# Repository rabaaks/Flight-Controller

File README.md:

# Custom Flight Controller

This is a custom flight controller and camera system that I designed to be used with Ardupilot for a drone or airplane. I made this to learn more about PCB design and also because I wanted a flight controller that I could use for my RC plane, so that I could setup autonomous flight and have better telemetry. I also wanted specific peripherals like the led strip and an OSD.

## Features

* STM32H743 Microcontroller
* BMP388 Pressure Sensor
* QMC5883 Magnetometeter
* ICM-42688 IMU
* OSD using MAX7456
* LED Strip
* 12 Motor Ouputs
* MicroSD Card
* 6 UARTs and 1 I2C

## Schematic

## PCB

## Render

I also designed a basic camera system to be used with it, using RX5808 and TX5823S modules. It uses a camera and display from a car backup camera system which was a low cost option that uses analog video. The camera and display require 12v, while the radio modules require 5v, so some voltage conversion is necessary. This circuit will be assembled on 0.1" pitch perfboard.

## Bill of Materials

|Name                                                               |Quantity|Unit Price|Total Price|Link                                                |FIELD6|Total Price|
|-------------------------------------------------------------------|--------|----------|-----------|----------------------------------------------------|------|-----------|
|CL10B105KA8NNNC                                                    |50      |0.0062    |0.31       |https://www.lcsc.com/product-detail/C29936.html     |      |71.26      |
|CL10B104KB8NNNC                                                    |100     |0.0027    |0.27       |https://www.lcsc.com/product-detail/C1591.html      |      |           |
|CL21B475KOFNNNE                                                    |10      |0.0191    |0.19       |https://www.lcsc.com/product-detail/C107365.html    |      |           |
|CL21B106KOQNNNE                                                    |10      |0.0247    |0.25       |https://www.lcsc.com/product-detail/C95841.html     |      |           |
|CL10C120JB8NNNC                                                    |100     |0.0047    |0.47       |https://www.lcsc.com/product-detail/C38523.html     |      |           |
|CL10B225KP8NNNC                                                    |50      |0.0123    |0.62       |https://www.lcsc.com/product-detail/C100082.html    |      |           |
|CL10C180JB8NNNC                                                    |100     |0.005     |0.5        |https://www.lcsc.com/product-detail/C1647.html      |      |           |
|CL10C470JB8NNNC                                                    |100     |0.0031    |0.31       |https://www.lcsc.com/product-detail/C1671.html      |      |           |
|CL31A226KOHNNNE                                                    |5       |0.0381    |0.19       |https://www.lcsc.com/product-detail/C90146.html     |      |           |
|CL21B104KBCNNNC                                                    |50      |0.0065    |0.33       |https://www.lcsc.com/product-detail/C1711.html      |      |           |
|SS54                                                               |10      |0.0433    |0.43       |https://www.lcsc.com/product-detail/C22452.html     |      |           |
|WS2812B-B/T                                                        |5       |0.0879    |0.44       |https://www.lcsc.com/product-detail/C2761795.html   |      |           |
|NCD0805R1                                                          |50      |0.0125    |0.63       |https://www.lcsc.com/product-detail/C84256.html     |      |           |
|ZX-XH2.54-3PZZ                                                     |20      |0.01      |0.2        |https://www.lcsc.com/product-detail/C7429633.html   |      |           |
|XT30PW-M30.G.Y                                                     |1       |0.2926    |0.29       |https://www.lcsc.com/product-detail/C431092.html    |      |           |
|TYPE-C 16PIN 2MD(073)                                              |20      |0.06      |1.2        |https://www.lcsc.com/product-detail/C2765186.html   |      |           |
|ZX-XH2.54-6PZZ                                                     |20      |0.0198    |0.4        |https://www.lcsc.com/product-detail/C7429636.html   |      |           |
|ZX-XH2.54-4PZZ                                                     |20      |0.0111    |0.22       |https://www.lcsc.com/product-detail/C7429634.html   |      |           |
|ZX-XH2.54-10PZZ                                                    |10      |0.0434    |0.43       |https://www.lcsc.com/product-detail/C7429640.html   |      |           |
|TF PUSH                                                            |10      |0.0568    |0.57       |https://www.lcsc.com/product-detail/C393941.html    |      |           |
|APH0630T6R8M                                                       |10      |0.0633    |0.63       |https://www.lcsc.com/product-detail/C5349706.html   |      |           |
|0603WAF5601T5E                                                     |100     |0.0012    |0.12       |https://www.lcsc.com/product-detail/C23189.html     |      |           |
|0603WAF1001T5E                                                     |100     |0.0012    |0.12       |https://www.lcsc.com/product-detail/C21190.html     |      |           |
|0603WAF5101T5E                                                     |100     |0.0012    |0.12       |https://www.lcsc.com/product-detail/C23186.html     |      |           |
|0603WAF1003T5E                                                     |100     |0.0011    |0.11       |https://www.lcsc.com/product-detail/C25803.html     |      |           |
|0603WAF750JT5E                                                     |100     |0.0013    |0.13       |https://www.lcsc.com/product-detail/C4275.html      |      |           |
|0603WAF1002T5E                                                     |100     |0.0011    |0.11       |https://www.lcsc.com/product-detail/C25804.html     |      |           |
|0603WAF3301T5E                                                     |100     |0.0012    |0.12       |https://www.lcsc.com/product-detail/C22978.html     |      |           |
|0603WAF2202T5E                                                     |100     |0.0012    |0.12       |https://www.lcsc.com/product-detail/C31850.html     |      |           |
|TPS54302DDCR                                                       |5       |0.1517    |0.76       |https://www.lcsc.com/product-detail/C311983.html    |      |           |
|BMP388                                                             |1       |2.7418    |2.74       |https://www.lcsc.com/product-detail/C779278.html    |      |           |
|QMC5883P                                                           |1       |1.48      |1.48       |https://www.lcsc.com/product-detail/C2847467.html   |      |           |
|STM32H743VIT6                                                      |1       |7.1333    |7.13       |https://www.lcsc.com/product-detail/C114409.html    |      |           |
|AT7456ELAH                                                         |1       |3.9151    |3.92       |https://www.lcsc.com/product-detail/C42388749.html  |      |           |
|ICM-42688-PC                                                       |1       |2.0211    |2.02       |https://www.lcsc.com/product-detail/C48586483.html  |      |           |
|X322527MSB4SI                                                      |10      |0.0718    |0.72       |https://www.lcsc.com/product-detail/C9008.html      |      |           |
|X322516MLB4SI                                                      |10      |0.0678    |0.68       |https://www.lcsc.com/product-detail/C13738.html     |      |           |
|X321532768KGD2SI                                                   |5       |0.2164    |1.08       |https://www.lcsc.com/product-detail/C620155.html    |      |           |
|KM477M025F12RR0VH2FP0                                              |10      |0.0393    |0.39       |https://www.lcsc.com/product-detail/C43839.html     |      |           |
|LED Strip 5m                                                       |1       |8.46      |8.46       |https://www.aliexpress.us/item/3256807796309465.html|      |           |
|MT3608 5pcs                                                        |1       |2.49      |2.49       |https://www.aliexpress.us/item/3256806175499915.html|      |           |
|MP1584 5pcs                                                        |1       |5.5       |5.5        |https://www.aliexpress.us/item/3256805119457659.html|      |           |
|RX5808                                                             |1       |12.76     |12.76      |https://www.aliexpress.us/item/3256808812641407.html|      |           |
|TX5823S                                                            |1       |9.07      |9.07       |https://www.aliexpress.us/item/3256808812641407.html|      |           |
|VS-S4301                                                           |1       |15.99     |15.99      |https://a.co/d/fmBpzXg                              |      |           |
|Bingfu Dual Band WiFi Antenna 2.4GHz 5/5.8GHz 3dBi SMA Male Antenna|1       |9.99      |9.99       |https://a.co/d/eEHf94O                              |      |           |
|4 Layer JLCPCB                                                     |1       |7         |7          |https://cart.jlcpcb.com/quote?stencilLayer=4        |      |           |

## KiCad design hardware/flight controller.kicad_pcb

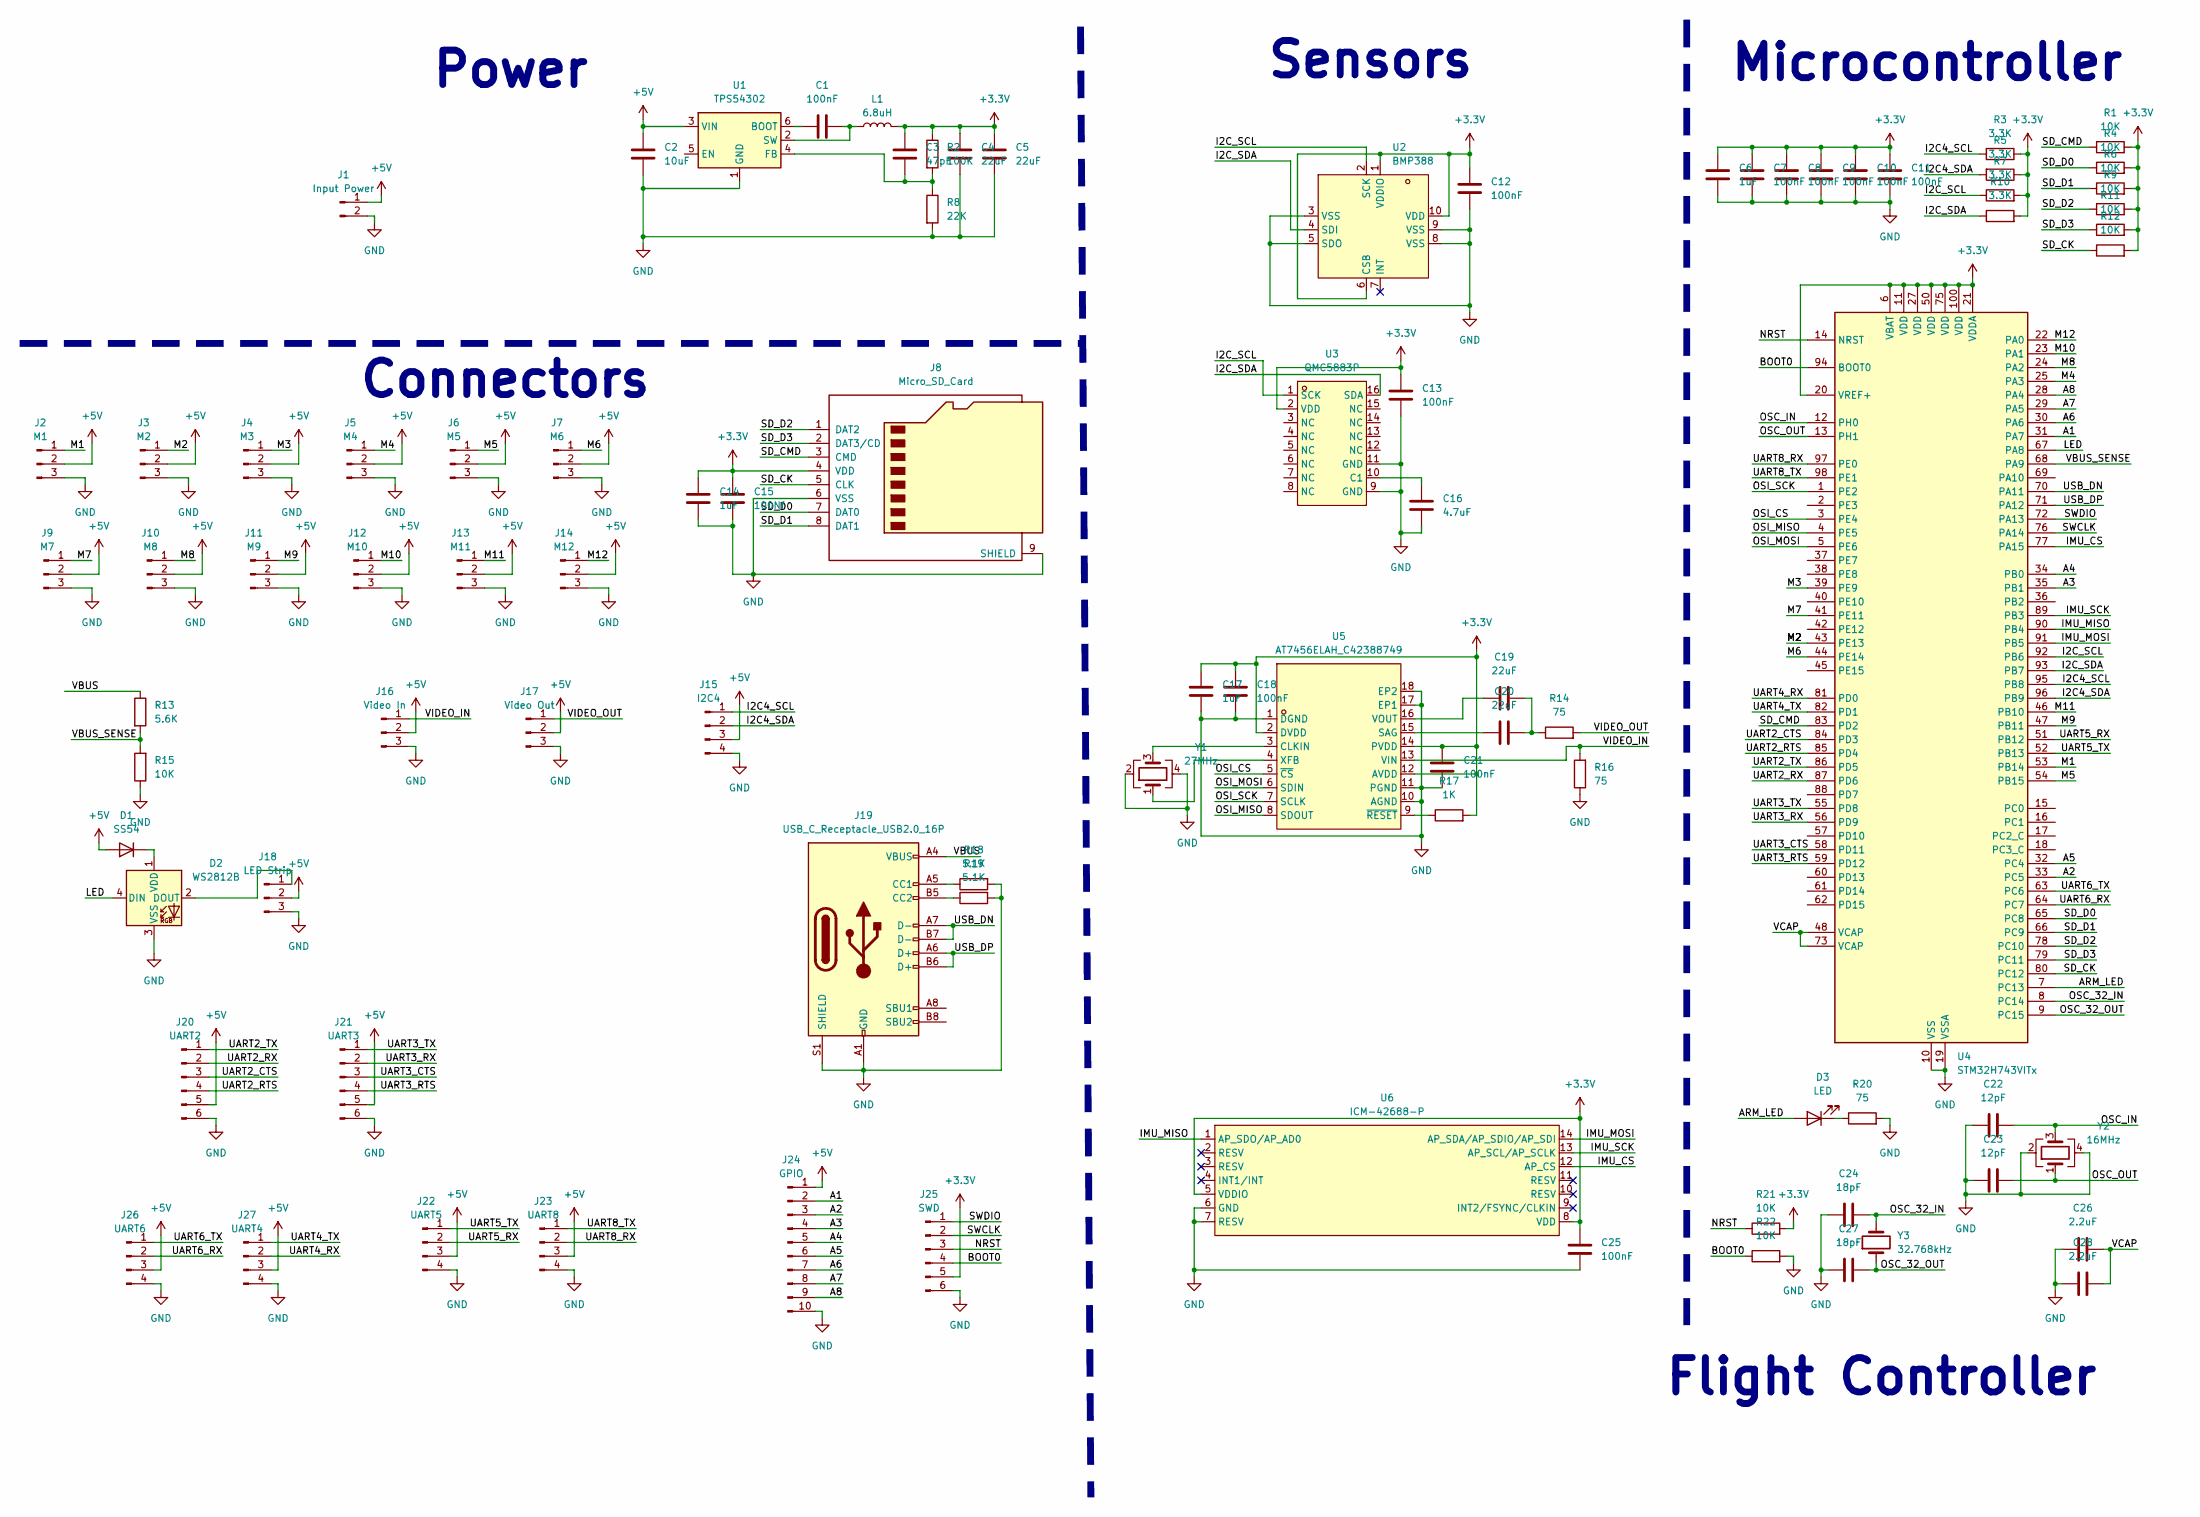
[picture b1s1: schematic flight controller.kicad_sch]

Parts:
C1, C7, C8, C9, C10, C11, C12, C13, C18, C21, C25: 100nF; C_0603_1608Metric
C2: 10uF; C_0805_2012Metric
C3: 47pF; C_0603_1608Metric
C4, C5, C19, C20: 22uF; C_1206_3216Metric
C6, C14, C17: 1uF; C_0603_1608Metric
C15: 100Nf; C_0603_1608Metric
C16: 4.7uF; C_0805_2012Metric
C22, C23: 12pF; C_0603_1608Metric
C24, C27: 18pF; C_0603_1608Metric
C26, C28: 2.2uF; C_0603_1608Metric
D1: SS54; D_SMA
D2: WS2812B; LED_WS2812B_PLCC4_5.0x5.0mm_P3.2mm
D3: LED; LED_0805_2012Metric
J1: Input Power; AMASS_XT30PW-M_1x02_P2.50mm_Horizontal
J2: M1; JST_XH_B3B-XH-A_1x03_P2.50mm_Vertical
J3: M2; JST_XH_B3B-XH-A_1x03_P2.50mm_Vertical
J4: M3; JST_XH_B3B-XH-A_1x03_P2.50mm_Vertical
J5: M4; JST_XH_B3B-XH-A_1x03_P2.50mm_Vertical
J6: M5; JST_XH_B3B-XH-A_1x03_P2.50mm_Vertical
J7: M6; JST_XH_B3B-XH-A_1x03_P2.50mm_Vertical
J8: Micro_SD_Card; TF-SMD_TF-PUSH
J9: M7; JST_XH_B3B-XH-A_1x03_P2.50mm_Vertical
J10: M8; JST_XH_B3B-XH-A_1x03_P2.50mm_Vertical
J11: M9; JST_XH_B3B-XH-A_1x03_P2.50mm_Vertical
J12: M10; JST_XH_B3B-XH-A_1x03_P2.50mm_Vertical
J13: M11; JST_XH_B3B-XH-A_1x03_P2.50mm_Vertical
J14: M12; JST_XH_B3B-XH-A_1x03_P2.50mm_Vertical
J15: I2C4; JST_XH_B4B-XH-A_1x04_P2.50mm_Vertical
J16: Video In; JST_XH_B3B-XH-A_1x03_P2.50mm_Vertical
J17: Video Out; JST_XH_B3B-XH-A_1x03_P2.50mm_Vertical
J18: LED Strip; JST_XH_B3B-XH-A_1x03_P2.50mm_Vertical
J19: USB_C_Receptacle_USB2.0_16P; USB_C_Receptacle_HCTL_HC-TYPE-C-16P-01A
J20: UART2; JST_XH_B6B-XH-A_1x06_P2.50mm_Vertical
J21: UART3; JST_XH_B6B-XH-A_1x06_P2.50mm_Vertical
J22: UART5; JST_XH_B4B-XH-A_1x04_P2.50mm_Vertical
J23: UART8; JST_XH_B4B-XH-A_1x04_P2.50mm_Vertical
J24: GPIO; JST_XH_B10B-XH-A_1x10_P2.50mm_Vertical
J25: SWD; JST_XH_B6B-XH-A_1x06_P2.50mm_Vertical
J26: UART6; JST_XH_B4B-XH-A_1x04_P2.50mm_Vertical
J27: UART4; JST_XH_B4B-XH-A_1x04_P2.50mm_Vertical
L1: 6.8uH; L_APV_APH0630
R1, R4, R6, R9, R11, R12, R15, R21, R22: 10K; R_0603_1608Metric
R2: 100K; R_0603_1608Metric
R3, R5, R7, R10: 3.3K; R_0603_1608Metric
R8: 22K; R_0603_1608Metric
R13: 5.6K; R_0603_1608Metric
R14, R16, R20: 75; R_0603_1608Metric
R17: 1K; R_0603_1608Metric
R18, R19: 5.1K; R_0603_1608Metric
U1: TPS54302; SOT-23-6
U2: BMP388; ST_HLGA-10_2x2mm_P0.5mm_LayoutBorder3x2y; LCSC Part C779278
U3: QMC5883P; LGA-16_3x3mm_P0.5mm; LCSC Part C2847467
U4: STM32H743VITx; LQFP-100_14x14mm_P0.5mm
U5: AT7456ELAH_C42388749; LGA-16_L6.8-W4.0-P0.65-TL-2EP; LCSC Part C42388749
U6: ICM-42688-P; LGA-14_3x2.5mm_P0.5mm_LayoutBorder3x4y; LCSC Part C1850418
Y1: 27MHz; Crystal_SMD_3225-4Pin_3.2x2.5mm
Y2: 16MHz; Crystal_SMD_3225-4Pin_3.2x2.5mm
Y3: 32.768kHz; Crystal_SMD_3215-2Pin_3.2x1.5mm

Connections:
+3.3V: C3.1, C4.2, C5.1, C6.2, C7.1, C8.2, C9.1, C10.2, C11.2, C12.2, C13.1, C14.2, C15.2, C17.1, C18.1, C21.1, C25.2, J8.4 (VDD), J25.5, L1.2, R1.2, R2.1, R3.1, R4.2, R5.1, R6.2, R7.2, R9.2, R10.2, R11.2, R12.2, R17.2, R21.2, U2.1 (VDDIO), U2.6 (CSB), U2.10 (VDD), U3.2 (VDD), U4.6 (VBAT), U4.11 (VDD), U4.20 (VREF+), U4.21 (VDDA), U4.27 (VDD), U4.50 (VDD), U4.75 (VDD), U4.100 (VDD), U5.2 (DVDD), U5.12 (AVDD), U5.14 (PVDD), U6.5 (VDDIO), U6.8 (VDD)
+5V: C2.1, D1.2 (A), J1.1, J2.2, J3.2, J4.2, J5.2, J6.2, J7.2, J9.2, J10.2, J11.2, J12.2, J13.2, J14.2, J15.3, J16.2, J17.2, J18.2, J20.5, J21.5, J22.3, J23.3, J24.1, J26.3, J27.3, U1.3 (VIN)
/A1: J24.2, U4.31 (PA7)
/A2: J24.3, U4.33 (PC5)
/A3: J24.4, U4.35 (PB1)
/A4: J24.5, U4.34 (PB0)
/A5: J24.6, U4.32 (PC4)
/A6: J24.7, U4.30 (PA6)
/A7: J24.8, U4.29 (PA5)
/A8: J24.9, U4.28 (PA4)
/ARM_LED: D3.2 (A), U4.7 (PC13)
/BOOT0: J25.4, R22.1, U4.94 (BOOT0)
/I2C4_SCL: J15.1, R3.2, U4.95 (PB8)
/I2C4_SDA: J15.2, R5.2, U4.96 (PB9)
/I2C_SCL: R7.1, U2.2 (SCK), U3.1 (SCK), U4.92 (PB6)
/I2C_SDA: R10.1, U2.4 (SDI), U3.16 (SDA), U4.93 (PB7)
/IMU_CS: U4.77 (PA15), U6.12 (AP_CS)
/IMU_MISO: U4.90 (PB4), U6.1 (AP_SDO/AP_AD0)
/IMU_MOSI: U4.91 (PB5), U6.14 (AP_SDA/AP_SDIO/AP_SDI)
/IMU_SCK: U4.89 (PB3), U6.13 (AP_SCL/AP_SCLK)
/LED: D2.4 (DIN), U4.67 (PA8)
/M1: J2.1, U4.53 (PB14)
/M2: J3.1, U4.43 (PE13)
/M3: J4.1, U4.39 (PE9)
/M4: J5.1, U4.25 (PA3)
/M5: J6.1, U4.54 (PB15)
/M6: J7.1, U4.44 (PE14)
/M7: J9.1, U4.41 (PE11)
/M8: J10.1, U4.24 (PA2)
/M9: J11.1, U4.47 (PB11)
/M10: J12.1, U4.23 (PA1)
/M11: J13.1, U4.46 (PB10)
/M12: J14.1, U4.22 (PA0)
/NRST: J25.3, R21.1, U4.14 (NRST)
/OSC_32_IN: C24.1, U4.8 (PC14), Y3.2
/OSC_32_OUT: C27.2, U4.9 (PC15), Y3.1
/OSC_IN: C22.1, U4.12 (PH0), Y2.3
/OSC_OUT: C23.2, U4.13 (PH1), Y2.1
/OSI_CS: U4.3 (PE4), U5.5 (~CS)
/OSI_MISO: U4.4 (PE5), U5.8 (SDOUT)
/OSI_MOSI: U4.5 (PE6), U5.6 (SDIN)
/OSI_SCK: U4.1 (PE2), U5.7 (SCLK)
/SD_CK: J8.5 (CLK), R12.1, U4.80 (PC12)
/SD_CMD: J8.3 (CMD), R1.1, U4.83 (PD2)
/SD_D0: J8.7 (DAT0), R4.1, U4.65 (PC8)
/SD_D1: J8.8 (DAT1), R6.1, U4.66 (PC9)
/SD_D2: J8.1 (DAT2), R9.1, U4.78 (PC10)
/SD_D3: J8.2 (DAT3/CD), R11.1, U4.79 (PC11)
/SWCLK: J25.2, U4.76 (PA14)
/SWDIO: J25.1, U4.72 (PA13)
/UART2_CTS: J20.3, U4.84 (PD3)
/UART2_RTS: J20.4, U4.85 (PD4)
/UART2_RX: J20.2, U4.87 (PD6)
/UART2_TX: J20.1, U4.86 (PD5)
/UART3_CTS: J21.3, U4.58 (PD11)
/UART3_RTS: J21.4, U4.59 (PD12)
/UART3_RX: J21.2, U4.56 (PD9)
/UART3_TX: J21.1, U4.55 (PD8)
/UART4_RX: J27.2, U4.81 (PD0)
/UART4_TX: J27.1, U4.82 (PD1)
/UART5_RX: J22.2, U4.51 (PB12)
/UART5_TX: J22.1, U4.52 (PB13)
/UART6_RX: J26.2, U4.64 (PC7)
/UART6_TX: J26.1, U4.63 (PC6)
/UART8_RX: J23.2, U4.97 (PE0)
/UART8_TX: J23.1, U4.98 (PE1)
/USB_DN: J19.A7 (D-), J19.B7 (D-), U4.70 (PA11)
/USB_DP: J19.A6 (D+), J19.B6 (D+), U4.71 (PA12)
/VBUS: J19.A4 (VBUS), J19.A9 (VBUS), J19.B4 (VBUS), J19.B9 (VBUS), R13.1
/VBUS_SENSE: R13.2, R15.2, U4.68 (PA9)
/VCAP: C26.1, C28.1, U4.48 (VCAP), U4.73 (VCAP)
/VIDEO_IN: J16.1, R16.2, U5.13 (VIN)
/VIDEO_OUT: J17.1, R14.2
GND: C2.2, C4.1, C5.2, C6.1, C7.2, C8.1, C9.2, C10.1, C11.1, C12.1, C13.2, C14.1, C15.1, C16.2, C17.2, C18.2, C21.2, C22.2, C23.1, C24.2, C25.1, C26.2, C27.1, C28.2, D2.3 (VSS), J1.2, J2.3, J3.3, J4.3, J5.3, J6.3, J7.3, J8.6 (VSS), J8.9 (SHIELD), J9.3, J10.3, J11.3, J12.3, J13.3, J14.3, J15.4, J16.3, J17.3, J18.3, J19.A1 (GND), J19.A12 (GND), J19.B1 (GND), J19.B12 (GND), J19.S1 (SHIELD), J20.6, J21.6, J22.4, J23.4, J24.10, J25.6, J26.4, J27.4, R8.2, R15.1, R16.1, R18.2, R19.2, R20.2, R22.2, U1.1 (GND), U2.3 (VSS), U2.5 (SDO), U2.8 (VSS), U2.9 (VSS), U3.9 (GND), U3.11 (GND), U4.10 (VSS), U4.19 (VSSA), U4.26 (VSS), U4.49 (VSS), U4.74 (VSS), U4.99 (VSS), U5.1 (DGND), U5.10 (AGND), U5.11 (PGND), U5.17 (EP1), U5.18 (EP2), U6.6 (GND), U6.7 (RESV), Y1.2, Y1.4, Y2.2, Y2.4
unnamed: C19.2, C20.2, R14.1
unnamed: D1.1 (K), D2.1 (VDD)
unnamed: D2.2 (DOUT), J18.1
unnamed: D3.1 (K), R20.1
unnamed: J19.A5 (CC1), R18.1
unnamed: J19.B5 (CC2), R19.1
unnamed: C1.2, U1.6 (BOOT)
unnamed: C3.2, R2.2, R8.1, U1.4 (FB)
unnamed: C1.1, L1.1, U1.2 (SW)
unnamed: C16.1, U3.10 (C1)
unnamed: U5.3 (CLKIN), Y1.3
unnamed: C20.1, U5.15 (SAG)
unnamed: C19.1, U5.16 (VOUT)
unnamed: U5.4 (XFB), Y1.1
unnamed: R17.1, U5.9 (~RESET)

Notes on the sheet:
Microcontroller
Connectors
Sensors
Flight Controller
Power

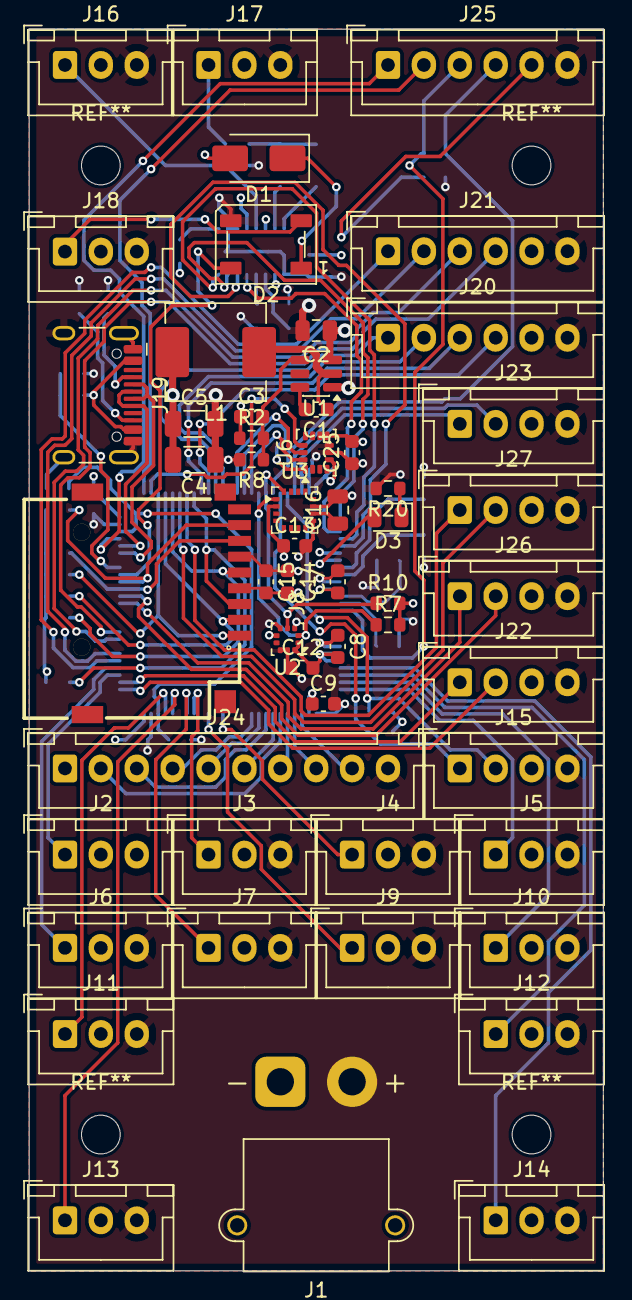
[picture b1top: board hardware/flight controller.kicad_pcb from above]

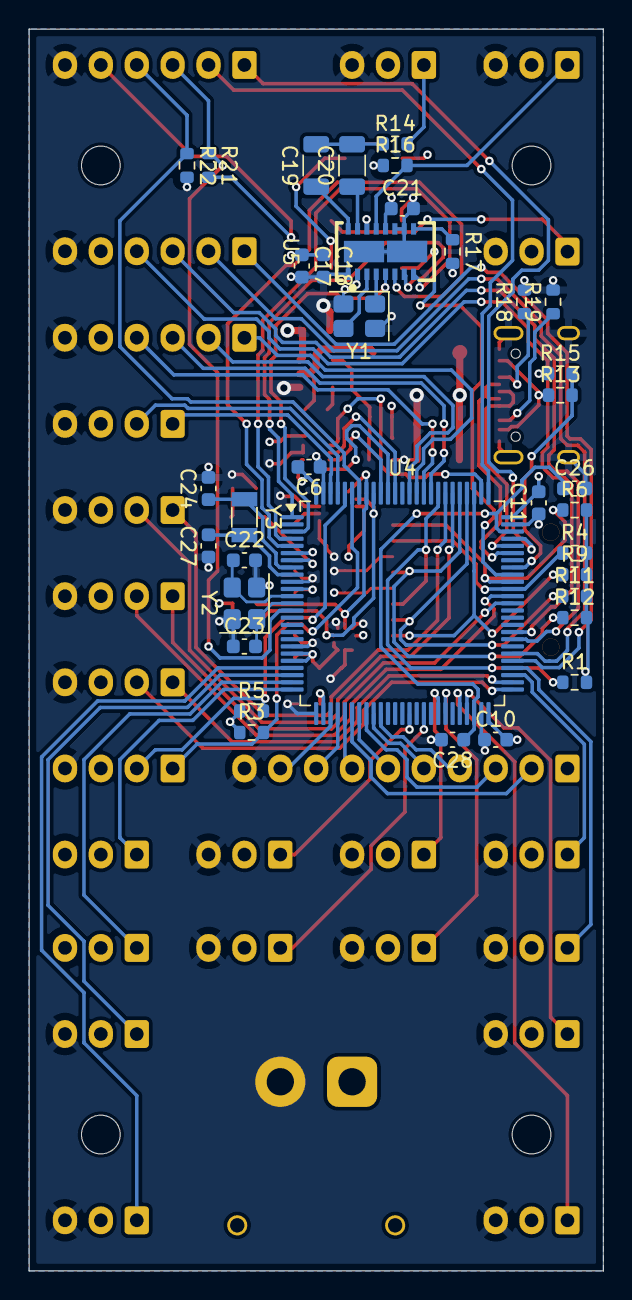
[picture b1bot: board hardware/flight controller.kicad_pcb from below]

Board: 4 copper layers, 40.0 x 86.5 mm, 90 parts (36 on the bottom side), 89 nets.
